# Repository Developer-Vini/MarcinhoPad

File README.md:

# MarcinhoPad

Custom macropad designed for the Hack Club Hackpad program.

## Overview

MarcinhoPad is a compact macro keyboard built around a Seeed XIAO RP2040. It features 6 mechanical switches, a rotary encoder for volume control, and an OLED display for visual feedback.

## Requirements Compliance

- MCU: Seeed XIAO RP2040 (through-hole)
- PCB: 2-layer, under 100mm x 100mm
- Case: 3D-printed only, fits within 200x200x100mm
- Inputs: 6 switches + 1 encoder (7 total, under 16 limit)
- Firmware: KMK (CircuitPython)

## Screenshots

### PCB

### Schematic

### Case
The case is 3D-printed in two parts (base + lid). See `production/case/` for STL files.

I couldn't place the 3D model of the PCB with the components inside the case because I wasn't able to export the 3D models in KiCad.

# Bill of Materials

| Designator | Quantity | Value | Footprint | Part Number |
|------------|----------|-------|-----------|-------------|
| U1 | 1 | Seeed XIAO RP2040 | XIAO-Generic-Hybrid-14P-2.54-21X17.8MM | Seeed XIAO RP2040 |
| U2 | 1 | 0.91" OLED SSD1306 | ER_OLEDM0.91_1x-I2C | 0.91" OLED I2C |
| SW1, SW2, SW3, SW4, SW5, SW6 | 6 | Tactile Switch 45° | SW_Cherry_MX_1.00u_PCB | Kailh Choc / compatible |
| SW10 | 1 | Rotary Encoder | RotaryEncoder_Alps_EC11E-Switch_Vertical_H20mm | Alps EC11E |
| D1, D2, D3, D4, D5, D6 | 6 | 1N4148 Diode | D_DO-35_SOD27_P7.62mm_Horizontal | 1N4148 |
| R1 | 1 | 330Ω Resistor | R_Axial_DIN0207_L6.3mm_D2.5mm_P7.62mm_Horizontal | 330Ω |

## Assembly Notes

- U1 (XIAO RP2040) is the main MCU, flashed with KMK firmware
- U2 (OLED) connects via I2C on D4 (SDA) and D5 (SCL)
- D1-D6 provide reverse polarity protection for switch matrix
- R1 is a current-limiting resistor for the OLED or indicator LED
- SW1-SW6 are the 6 key switches
- SW10 is the rotary encoder with integrated push button

## Firmware

The firmware is written in KMK for CircuitPython.

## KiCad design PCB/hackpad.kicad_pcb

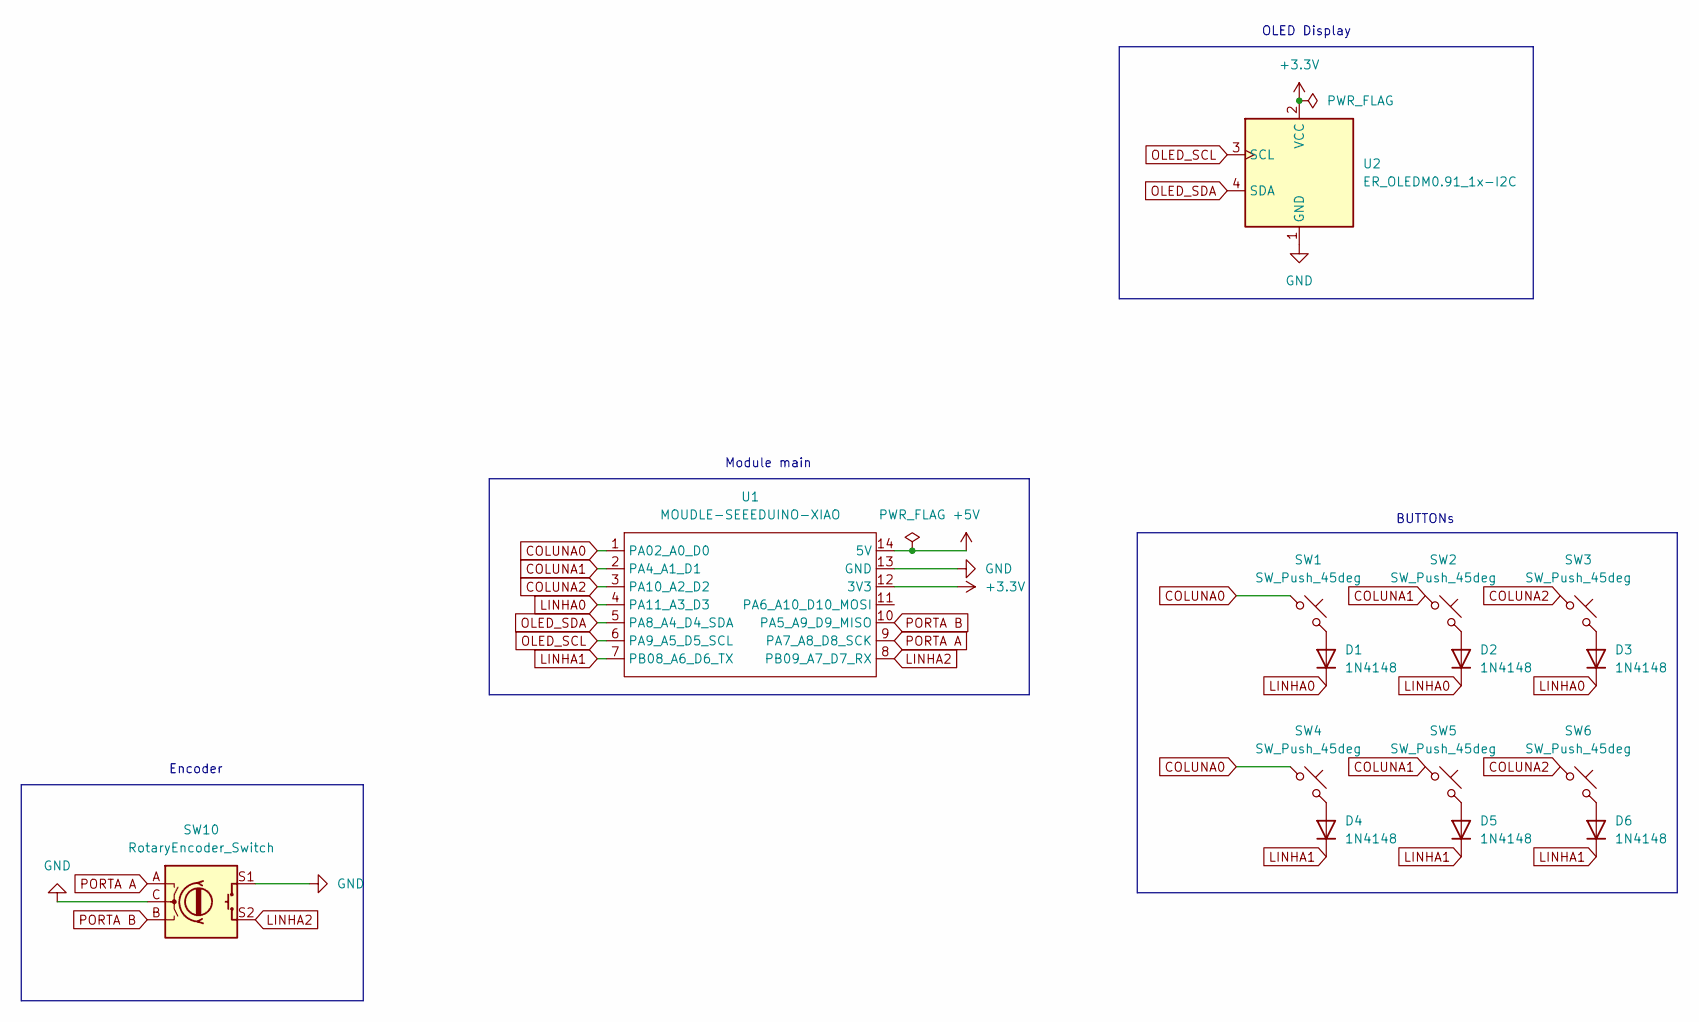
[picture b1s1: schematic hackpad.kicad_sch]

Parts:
D1, D2, D3, D4, D5, D6: 1N4148; D_DO-35_SOD27_P7.62mm_Horizontal
SW1, SW2, SW3, SW4, SW5, SW6: SW_Push_45deg; SW_Cherry_MX_1.00u_PCB
SW10: RotaryEncoder_Switch; RotaryEncoder_Alps_EC11E-Switch_Vertical_H20mm
U1: MOUDLE-SEEEDUINO-XIAO; XIAO-Generic-Hybrid-14P-2.54-21X17.8MM
U2: ER_OLEDM0.91_1x-I2C

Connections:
+3.3V: U1.12 (3V3), U2.2 (VCC)
+5V: U1.14 (5V)
COLUNA0: SW1.1, SW4.1, U1.1 (PA02_A0_D0)
COLUNA1: SW2.1, SW5.1, U1.2 (PA4_A1_D1)
COLUNA2: SW3.1, SW6.1, U1.3 (PA10_A2_D2)
GND: SW10.C, SW10.S1, U1.13 (GND), U2.1 (GND)
LINHA0: D1.1 (K), D2.1 (K), D3.1 (K), U1.4 (PA11_A3_D3)
LINHA1: D4.1 (K), D5.1 (K), D6.1 (K), U1.7 (PB08_A6_D6_TX)
LINHA2: SW10.S2, U1.8 (PB09_A7_D7_RX)
unnamed: D1.2 (A), SW1.2
unnamed: D2.2 (A), SW2.2
unnamed: D3.2 (A), SW3.2
unnamed: D4.2 (A), SW4.2
unnamed: D5.2 (A), SW5.2
unnamed: D6.2 (A), SW6.2
OLED_SCL: U1.6 (PA9_A5_D5_SCL), U2.3 (SCL)
OLED_SDA: U1.5 (PA8_A4_D4_SDA), U2.4 (SDA)
PORTA A: SW10.A, U1.9 (PA7_A8_D8_SCK)
PORTA B: SW10.B, U1.10 (PA5_A9_D9_MISO)

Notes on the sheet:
Encoder
Module main
OLED Display
BUTTONs

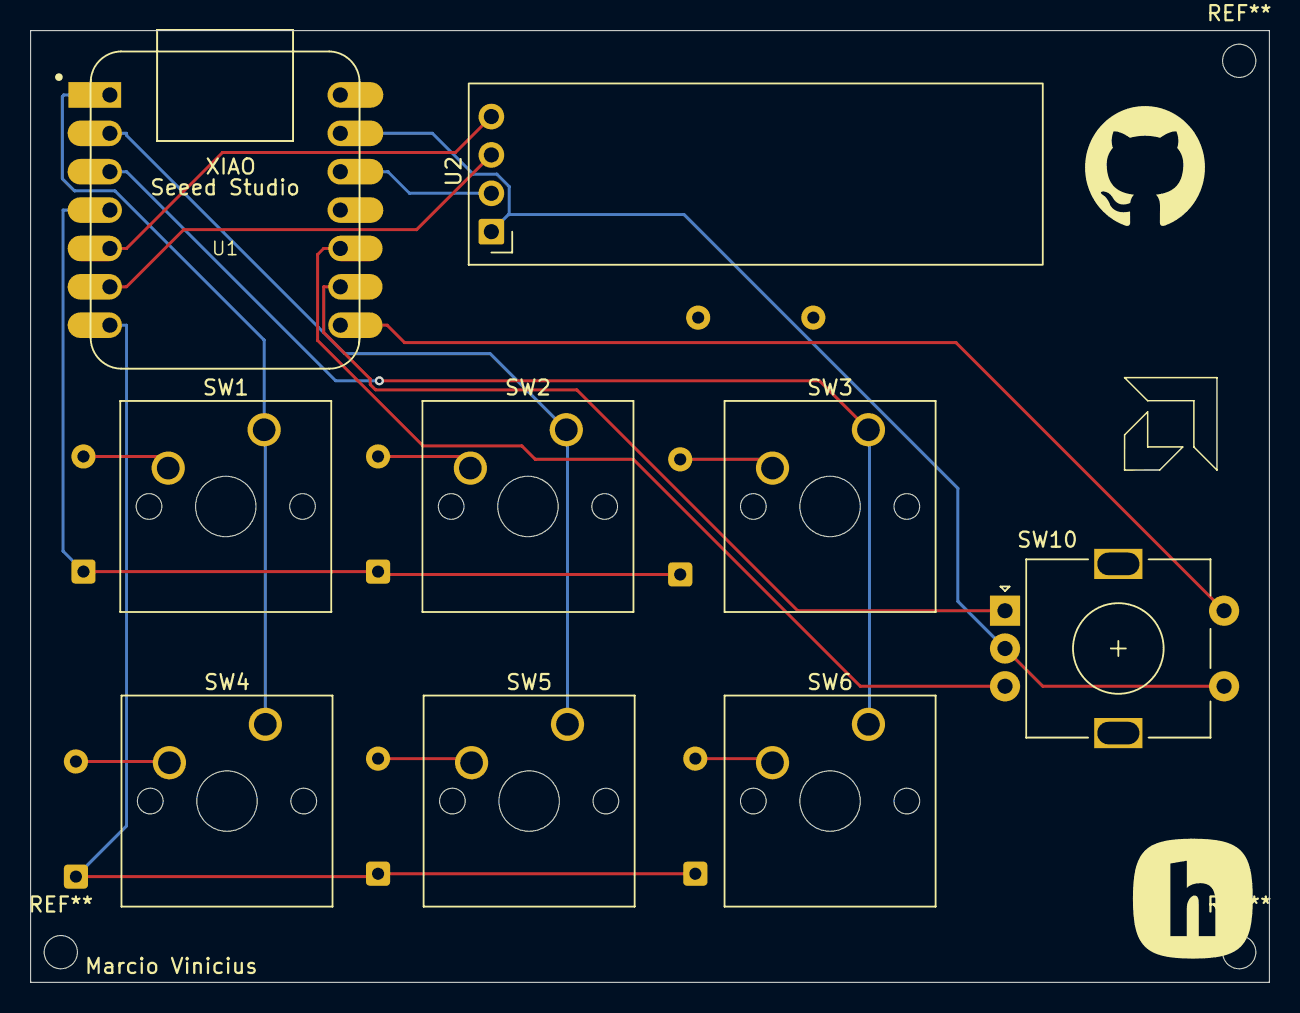
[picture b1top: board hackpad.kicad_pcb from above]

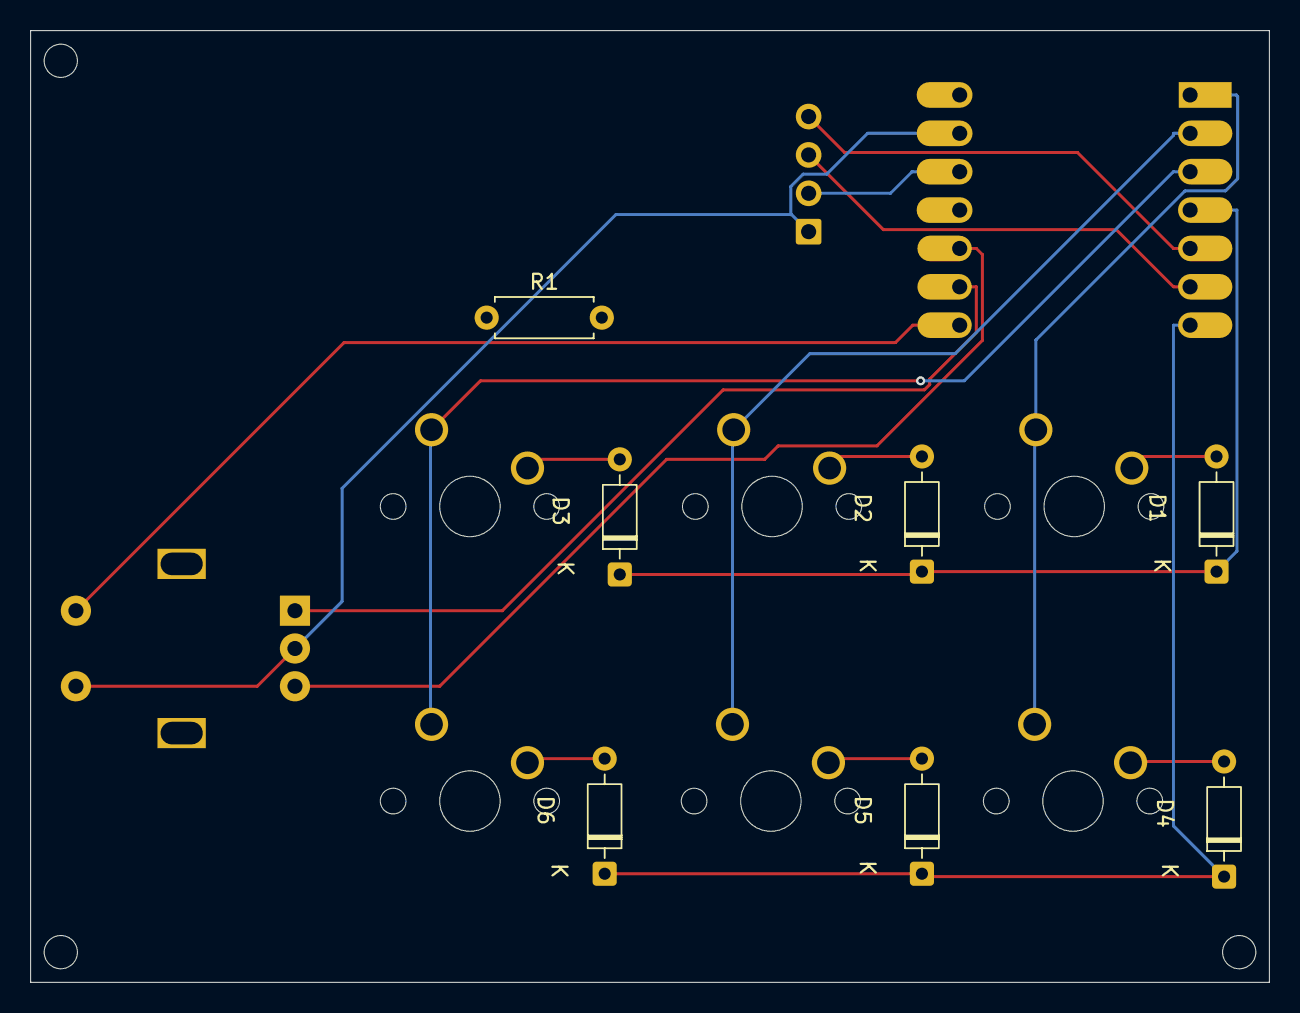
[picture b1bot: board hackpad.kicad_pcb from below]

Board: 2 copper layers, 82.0 x 63.0 mm, 16 parts (7 on the bottom side), 18 nets.

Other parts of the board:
R1: 330R; R_Axial_DIN0207_L6.3mm_D2.5mm_P7.62mm_Horizontal

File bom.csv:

Designator,Footprint,Quantity,Value,LCSC Part #
"D1, D2, D3, D4, D5, D6",D_DO-35_SOD27_P7.62mm_Horizontal,6,1N4148,
R1,R_Axial_DIN0207_L6.3mm_D2.5mm_P7.62mm_Horizontal,1,330R,
"SW1, SW2, SW3, SW4, SW5, SW6",SW_Cherry_MX_1.00u_PCB,6,SW_Push_45deg,
SW10,RotaryEncoder_Alps_EC11E-Switch_Vertical_H20mm,1,RotaryEncoder_Switch,
U1,XIAO-Generic-Hybrid-14P-2.54-21X17.8MM,1,MOUDLE-SEEEDUINO-XIAO,
U2,ER_OLEDM0.91_1x-I2C,1,ER_OLEDM0.91_1x-I2C,
